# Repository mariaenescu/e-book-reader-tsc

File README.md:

Enescu Maria - 331CA

# OpenBook Project - E-Book Reader

OpenBook is a compact device designed for digital reading. Based on the ESP32-C6 microcontroller, OpenBook includes integrated Wi-Fi connectivity.
It features a 7.5" e-Paper display and an 1800mAh battery, offering extended battery life.

--- 

## 3D Visualizations

---
## Block Diagram

---

## Main Components Overview

**Microcontroller – ESP32-C6-WROOM-1-N8**  
Acts as the main processing unit of the system, responsible for wireless communication, power management, and control of all peripherals. It uses SPI, I2C, and GPIO interfaces to interact with external modules.

**E-Paper Display – 7.5” Waveshare**  
Displays e-book content using ultra-low power. It is controlled via SPI and connected through MOSI, MISO, SCK, CS, DC, RST, and BUSY pins.

**MicroSD Card – 112A-TAAR-R03**  
Used for storing e-books and data files. Communicates with the ESP32 via the SPI interface and supports FAT32 format up to 32GB.

**NOR Flash Memory – W25Q512JVEIQ**  
Provides external non-volatile memory for storing firmware or additional data. It connects via SPI and supports fast read/write operations.

**Real-Time Clock – DS3231SN**  
Ensures accurate timekeeping, even when the device is off. It uses the I2C protocol and provides a 32KHz output and interrupt signal.

**Environmental Sensor – BME688**  
Measures temperature, humidity, pressure, and gas levels. Communicates via I2C and is powered through a dedicated I2C power pin.

**Battery – Cellevia LP584174 (Li-Po 3.7V, 1800mAh)**  
Powers the system when disconnected from USB. Provides stable operation and extended autonomy.

**Power Management – MCP73831 & AMS1117**  
MCP73831 handles Li-Po charging via USB-C. AMS1117 regulates the output voltage to 3.3V required by the ESP32 and peripherals.

**USB-C Connector – USB4110-GF-A**  
Used for charging the battery and data transfer. Protected by ESD varistor (PFMF.050.1) and Schottky diode for reverse polarity.

**Buttons – Tactile Push Buttons (3x)**  
Used for boot, reset, and mode change. Connected to GPIOs for user input and state control.

---

## Bill of Materials
| Compound                | Purchase                          | Datasheet                                                                                                                                                          |
|---------------------------|--------------------------------------------------------------------------------------------------------------------------------------------------------------------------------------------------------------------------------------------------------------------|--------------------------------------------------------------------------------------------------------------------------------------------------------------------|
| Buton                     | [Click here](https://componentsearchengine.com/prices/TSP1C-RA?manufacturer=KNITTER-SWITCH)                                                                                                                                                                        | https://docs.rs-online.com/1fd0/0900766b80e2c247.pdf                                                                                                   |
| Condensator 100nF         | [Click here](https://ro.mouser.com/ProductDetail/KYOCERA-AVX/04026D104KAT2A?qs=LLG2yGGJ5NhILwMziGI8Xg%3D%3D)                                                                                                                                                       | https://www.mouser.com/catalog/supplier/library/pdf/AVXSurfaceMountCeramic.pdf                                                                         |
| CPH3225A(C10_SUPERCAP)    | [Click here](https://ro.mouser.com/ProductDetail/Seiko-Semiconductors/CPH3225A?qs=3etwrb1wR%252BhUOph6lAO7eg%3D%3D)                                                                                                                                                | https://ro.mouser.com/datasheet/2/360/Seiko_Instruments_MicroBattery_E_20230330_2024Jan_-3561061.pdf                                                   |
| Condensator 4.7uF         | [Click here](https://ro.mouser.com/ProductDetail/KEMET/C0402C475M7PACTU?qs=SzIX745sIXFB9Q9KfZhc4g%3D%3D)                                                                                                                                                           | https://ro.mouser.com/datasheet/2/447/KEM_C1006_X5R_SMD-3316465.pdf                                                                                    |
| Tantalum Condensator 100uF | [Click here](https://ro.mouser.com/ProductDetail/KYOCERA-AVX/TAJW107M010RNJ?qs=Wtp%252Bf%2FAeVqIH8v1VxV%252B1Rg%3D%3D)                                                                                                                                             | https://ro.mouser.com/datasheet/2/40/TAJ-3165264.pdf                                                                                                   |
| Condensator 1uF           | [Click here](https://ro.mouser.com/ProductDetail/KYOCERA-AVX/04026D105KAT2A?qs=LLG2yGGJ5NgAzk5fb%252BnzGQ%3D%3D)                                                                                                                                                   | https://ro.mouser.com/datasheet/2/40/cx5r_KGM-3223198.pdf                                                                                              |
| Condensator 10uF          | [Click here](https://www.digikey.com/en/products/detail/venkel/C0402X5R100-106MNP/12327194)                                                                                                                                                                        | https://venkelecd.com/partnumber/datasheet/C0402X5R100-106MNP)                                                                                         |
| CHG_LED                   | [Click here](https://www.kingbrightusa.com/distyPNInv.asp?sltSearch=distyInv&match=1&txtPartNo=APHM1608ECT)                                                                                                                                                        | https://www.kingbrightusa.com/images/catalog/SPEC/APHM1608ECT.pdf                                                                                      |
| USBLC6-2SC6Y              | [Click here](https://ro.mouser.com/ProductDetail/STMicroelectronics/USBLC6-2SC6Y?qs=gNDSiZmRJS%2FOgDexvXkdow%3D%3D)                                                                                                                                                | https://ro.mouser.com/datasheet/2/389/usblc6_2sc6y-1852505.pdf                                                                                         |
| PGB1010603MR              | [Click here](https://ro.mouser.com/ProductDetail/Littelfuse/PGB1010603MR?qs=gu7KAQ731URLg4GSnNNN7Q%3D%3D)                                                                                                                                                          | https://www.littelfuse.com/assetdocs/pulseguard-esd-suppressors-pgb1-datasheet?assetguid=8a337998-d54d-466b-be4e-dc5bcd1f9321                          |
| SD0805S020S1R0            | [Click here](https://ro.mouser.com/ProductDetail/KYOCERA-AVX/SD0805S020S1R0?qs=jCA%252BPfw4LHbpkAoSnwrdjw%3D%3D)                                                                                                                                                   | https://ro.mouser.com/datasheet/2/40/schottky-3165252.pdf                                                                                              |
| MBR0530                   | [Click here](https://ro.mouser.com/ProductDetail/onsemi/MBR0530T1G?qs=3JMERSakeboS%2FFOxJUMWeg%3D%3D)                                                                                                                                                              | https://www.onsemi.com/download/data-sheet/pdf/mbr0530t1-d.pdf                                                                                         |
| Condensator 1uF/50V       | [Click here](https://ro.mouser.com/ProductDetail/KYOCERA-AVX/06035D105MAT2A?qs=k4kUdCzLgS5%252BURKe1SOIeQ%3D%3D)                                                                                                                                                   | https://ro.mouser.com/datasheet/2/40/cx5r_KGM-3223198.pdf                                                                                              |
| Condensator 0.1uF/50V     | [Click here](https://ro.mouser.com/ProductDetail/KYOCERA-AVX/04025C104JAT2A?qs=yqaQSyyJnNjAUYBPnTRwrw%3D%3D)                                                                                                                                                       | https://ro.mouser.com/datasheet/2/40/AutoMLCC-2952695.pdf                                                                                              |
| BD5229G-TR                | [Click here](https://ro.mouser.com/ProductDetail/ROHM-Semiconductor/BD5229G-TR?qs=4kLU8WoGk0vvnhrrYwdszw%3D%3D)                                                                                                                                                    | https://fscdn.rohm.com/en/products/databook/datasheet/ic/power/voltage_detector/bd52xxg-e.pdf                                                          |
| XC6220A331MR-G            | [Click here](https://ro.mouser.com/ProductDetail/Torex-Semiconductor/XC6220A331MR-G?qs=AsjdqWjXhJ8ZSWznL1J0gg%3D%3D)                                                                                                                                               | https://ro.mouser.com/datasheet/2/760/xc6220-3371556.pdf                                                                                               |
| FH34SRJ-24S-0.5SH_99_     | [Click here](https://ro.mouser.com/ProductDetail/Hirose-Connector/FH34SRJ-24S-0.5SH99?qs=vcbW%252B4%252BSTIpKBl5ap9J8Fw%3D%3D)                                                                                                                                     | https://ro.mouser.com/datasheet/2/185/FH34SRJ_24S_0_5SH_99__CL0580_1255_6_99_2DDrawing_0-1615044.pdf                                                   |
| USB4110-GF-A              | [Click here](https://ro.mouser.com/ProductDetail/GCT/USB4110-GF-A?qs=KUoIvG%2F9IlYiZvIXQjyJeA%3D%3D)                                                                                                                                                               | https://ro.mouser.com/datasheet/2/837/GCT_USB4110_Product_Drawing___20k_cycles-3455479.pdf                                                             |
| QWIIC_RIGHT_ANGLE         | [Click here](https://ro.mouser.com/ProductDetail/JST-Commercial/SM04B-SRSS-TBLFSN?qs=cdbOS8ANM9B3FdyA6cNU2A%3D%3D)                                                                                                                                                 | https://ro.mouser.com/datasheet/2/564/eSR_SZ-3476820.pdf                                                                                               |
| 112A-TAAR-R03_ATTEND      | [Click here](https://www.tme.eu/ro/details/mcc-sdmicro/conectori-pentru-cartele/attend/112a-taar-r03/?utm_source=google&utm_medium=cpc&utm_campaign=RUMUNIA%20%5BP%5D%5BDC%5D&gclsrc=aw.ds&gad_source=1&gclid=Cj0KCQjwhr6_BhD4ARIsAH1YdjAAB3boEl8CsGuWhO_BI6GGNh3SIUi2gO3ftspK5-ah9niT38KGMasaAnHZEALw_wcB) | https://www.attend.com.tw/data/download/file/112A-TAAR-R03.pdf                                                                                         |
| Bobina                    | [Click here](https://ro.mouser.com/ProductDetail/Wurth-Elektronik/744043680?qs=PGXP4M47uW6VkZq%252BkzjrHA%3D%3D)                                                                                                                                                   | https://www.we-online.com/components/products/datasheet/744043680.pdf                                                                                  |
| MCP73831                  | [Click here](https://ro.mouser.com/ProductDetail/Microchip-Technology/MCP73831T-2ATI-OT?qs=yUQqVecv4qsZbioEUu%252B83g%3D%3D)                                                                                                                                       | https://ro.mouser.com/datasheet/2/268/MCP73831_Family_Data_Sheet_DS20001984H-3441711.pdf                                                               |
| PFMF.050.1                | [Click here](https://ro.mouser.com/ProductDetail/Schurter/PFMF.050.2?qs=1auRipcfynCums5v1iucSA%3D%3D)                                                                                                                                                              | https://ro.mouser.com/datasheet/2/358/typ_PFMF-1275918.pdf                                                                                             |
| DMG2305UX-7               | [Click here](https://ro.mouser.com/ProductDetail/Diodes-Incorporated/DMG2305UX-7?qs=L1DZKBg7t5F%2FNBHrjfxC%252Bg%3D%3D)                                                                                                                                            | https://www.diodes.com/assets/Datasheets/DMG2305UX.pdf                                                                                                 |
| SI1308EDL-T1-GE3          | [Click here](https://ro.mouser.com/ProductDetail/Vishay-Semiconductors/SI1308EDL-T1-GE3?qs=bX1%252BNvsK%2FBramh9tgpOaEw%3D%3D)                                                                                                                                     | https://www.vishay.com/docs/63399/si1308edl.pdf                                                                                                        |
| Rezistenta 10K            | [Click here](https://www.digikey.com/en/products/detail/venkel/CR0402-10W-102JT/12332774)                                                                                                                                                                          | https://data.venkel.com/documents/cr-series?_gl=1*2989pu*_ga*Nzc4NDIxNDY2LjE3NDM3NTUzNDM.*_ga_JRKGBZNVM8*MTc0Mzc1NTM0My4xLjAuMTc0Mzc1NTM0My42MC4wLjA.) |
| Rezistenta 200            | [Click here](https://ro.mouser.com/ProductDetail/Vishay-Beyschlag/MCS0402MD2000BE100?qs=3SvaY9RawMJNVte4F12%252BZQ%3D%3D)                                                                                                                                          | https://www.vishay.com/docs/28952/mcs0402at-mct0603at-mcu0805at-mca1206at.pdf                                                                          |
| Rezistenta 100K           | [Click here](https://www.digikey.com/en/products/detail/venkel/CR0402-16W-1003FT/12328296)                                                                                                                                                                         | https://octopart.com/datasheet/cr0402-16w-1003ft-venkel-16112934)                                                                                      |
| Rezistenta 2.2            | [Click here](https://www.digikey.com/en/products/detail/venkel/TFCR0402-16W-C-1002BT/12331302)                                                                                                                                                                     | https://data.venkel.com/documents/tfcr-series?_gl=1*1o1n72f*_ga*Nzc4NDIxNDY2LjE3NDM3NTUzNDM.*_ga_JRKGBZNVM8*MTc0Mzc1NTM0My4xLjEuMTc0Mzc1NjA4Mi4yMi4wLjA.) |
| Rezistenta 5K1            | [Click here](https://ro.mouser.com/ProductDetail/YAGEO/RT0402BRD075K1L?qs=gY0y7AQI9SOxpEAvlEsiTQ%3D%3D)                                                                                                                                                            | https://ro.mouser.com/datasheet/2/447/PYu_RT_1_to_0_01_RoHS_L_15-3461507.pdf                                                                           |
| Rezistenta 2K             | [Click here](https://ro.mouser.com/ProductDetail/Bourns/CR0402AFX-2001GLF?qs=GedFDFLaBXEKjamDtfYtIQ%3D%3D)                                                                                                                                                         | https://ro.mouser.com/datasheet/2/54/cr_a-1858337.pdf                                                                                                  |
| Rezistenta 0.47           | [Click here](https://ro.mouser.com/ProductDetail/Vishay-Beyschlag/MMA02040C4707JB000?qs=YmMt7wOBEV42V6C1Rc7zpg%3D%3D)                                                                                                                                              | https://www.vishay.com/docs/28713/melfprof.pdf                                                                                                         |
| Rezistenta 15             | [Click here](https://ro.mouser.com/ProductDetail/YAGEO/RT0402FRE0715RL?qs=BXCcY9r%252B08DFFpLSkPOIqQ%3D%3D)                                                                                                                                                        | https://ro.mouser.com/datasheet/2/447/PYu_RT_1_to_0_01_RoHS_L_15-3461507.pdf                                                                           |
| BME688                    | [Click here](https://ro.mouser.com/ProductDetail/Bosch-Sensortec/BME688?qs=IS%252B4QmGtzzqQoVDscqwx3A%3D%3D)                                                                                                                                                       | https://ro.mouser.com/datasheet/2/783/bst_bme688_fl000-2307034.pdf                                                                                     |
| W25Q512JVEIQ              | [Click here](https://ro.mouser.com/ProductDetail/Winbond/W25Q512JVEIQ?qs=l7cgNqFNU1jw6svr3at6tA%3D%3D)                                                                                                                                                             | https://ro.mouser.com/datasheet/2/949/Winbond_W25Q512JV_Datasheet-3240039.pdf                                                                          |
| ESP32-C6-WROOM-1-N8       | [Click here](https://ro.mouser.com/ProductDetail/Espressif-Systems/ESP32-C6-WROOM-1-N8?qs=8Wlm6%252BaMh8ST02Gmwp74cw%3D%3D)                                                                                                                                        | https://ro.mouser.com/datasheet/2/891/Espressif_ESP32_C6_WROOM_1__Datasheet_V0_1_PRELIMI-3239987.pdf                                                   |
| DS3231SN#                 | [Click here](https://ro.mouser.com/ProductDetail/Analog-Devices-Maxim-Integrated/DS3231SN?qs=1eQvB6Dk1vhUlr8%2FOrV0Fw%3D%3D)                                                                                                                                       | https://ro.mouser.com/datasheet/2/609/DS3231-3421123.pdf                                                                                               |
| MAX17048G+T10             | [Click here](https://ro.mouser.com/ProductDetail/Analog-Devices-Maxim-Integrated/MAX17048G%2bT10?qs=D7PJwyCwLAoGnnn8jEPRBQ%3D%3D)                                                                                                                                  | https://ro.mouser.com/datasheet/2/609/MAX17048_MAX17049-3469099.pdf                                                                                    |
---

## Hardware Functionality Description

The project uses the `ESP32-C6-WROOM-1-N8` microcontroller, which integrates **BLE 5** and **Wi-Fi 6** for fast and efficient communication.
The system is powered by a **3.7V Li-Po battery** with a capacity of 1800mAh (`Cellevia LP584174`).
Battery charging is managed by the `TP4056` module via a `USB-C` connector, and the constant `3.3V` required by the system is provided by an `AMS1117` voltage regulator.
The `ESP32-C6` microcontroller controls the entire system through standard **SPI**, **I2C**, and **GPIO** interfaces, as follows:
1. The `7.5" Waveshare e-Paper Display` (800x480 resolution) is connected via SPI.
2. The `SD Card` and `external NOR Flash` memory are also connected via SPI for data storage.
3. The `RTC (DS3231SN)` and `environmental sensor (BME688)` are connected via **I2C**, enabling precise real-time measurements.
4. **GPIO connections** allow control of the `RESET` and `BOOT` functions, and the **Qwiic/Stemma QT** interface supports additional sensor expansion.
5. For debugging, there are dedicated Test Pads for UART communication (`TX/RX`).

---

##  Pinii ESP32-C6
| Pin ESP32-C6 | GPIO        | Job            | Connected to          |
|--------------|-------------|--------------------|------------------------|
| EN           | -           | RESET              | Reset hardware         |
| IO0          | GPIO0       | INT RTC            | Intrerupere RTC        |
| IO1          | GPIO1       | 32KHZ              | Semnal 32kHz RTC       |
| IO2          | GPIO2       | MISO               | SPI MISO (Date citite) |
| IO3          | GPIO3       | EPD BUSY           | Semnal ocupat Display  |
| IO4          | GPIO4       | SS_SD              | Chip select SD Card    |
| IO5          | GPIO5       | EPD_DC             | Comanda/Date Display   |
| IO6          | GPIO6       | SCK                | SPI Clock              |
| IO7          | GPIO7       | MOSI               | SPI MOSI (Date trimise)|
| IO8          | GPIO8       | IO/BOOT            | Boot mode selection    |
| IO9          | GPIO9       | -                  | Neconectat             |
| IO10         | GPIO10      | -                  | Neconectat             |
| IO11         | GPIO11      | EPD_CS             | Chip Select Display    |
| IO12         | GPIO12      | FLASH_CS           | Chip Select Flash      |
| IO13         | GPIO13      | USB D-             | Linie USB D-           |
| IO14         | GPIO14      | USB D+             | Linie USB D+           |
| IO15         | GPIO15      | IO/CHANGE          | Buton schimbare mod    |
| IO16         | GPIO16/TX   | TX                 | UART Debug TX          |
| IO17         | GPIO17/RX   | RX                 | UART Debug RX          |
| IO18         | GPIO18      | RTC_RST            | Reset RTC              |
| IO19         | GPIO19      | I2C PW             | Alimentare senzor I2C  |
| IO20         | GPIO20      | EPD_3V3_C          | Control 3.3V Display   |
| IO21         | GPIO21/SDA  | SDA                | I2C Date               |
| IO22         | GPIO22/SCL  | SCL                | I2C Clock              |
| IO23         | GPIO23      | EPD_RST            | Reset Display          |
---

## Project Implementation:
      
`The schematic` was created according to the requirement PDF, using symbols from the provided library and verified using 
the `ERC` file. Warnings were avoided, and remaining errors were accepted as non-critical.
During the `PCB` design phase, all components were placed exclusively on the `Top Layer`, following mechanical and dimensional recommendations.
Both the `ESP32 antenna area` and the `buttons` were cut out from the PCB outline.
`Routing` was performed using the Autorouter, with a 100% routing weight and minimum via size.
A `ground plane` was created on both layers (Bottom and Top).
`Via stitching` was added near the ESP32 component in a free area, avoiding routing traces.
Each component name is marked with `TopSilkscreen`.
Each component has an associated 3D model, either designed (TPs, battery, and display) or imported from external libraries.
The 3D models were created using exact dimensions from the provided datasheets and can be viewed in the `Images/` folder.
Later, I positioned the 3D model of the PCB, the battery, and the display inside the case.
A video has also been added in `Images/` to visualize the 3D placement of all components for the complete E-Book.

---

### Issues Encountered:

- After importing each 3D component, I noticed several routing errors and value mismatches appearing on the PCB—
  errors that did not exist before using `Push to 3D PCB`. After adding the 3D components, I attempted to re-route to fix these issues.
- I encountered problems with 3D component placement. Although all 3D models were imported, not all of them appeared on the 3D PCB.
- In **Fusion 360**, `Push to 3D PCB` sometimes desynchronized component labels and layers. Also, not all components kept their footprints aligned after 3D model imports, requiring manual corrections.
- I also had to ensure no 90° trace angles were present, per assignment constraints — which was hard to maintain while autorouting.

---

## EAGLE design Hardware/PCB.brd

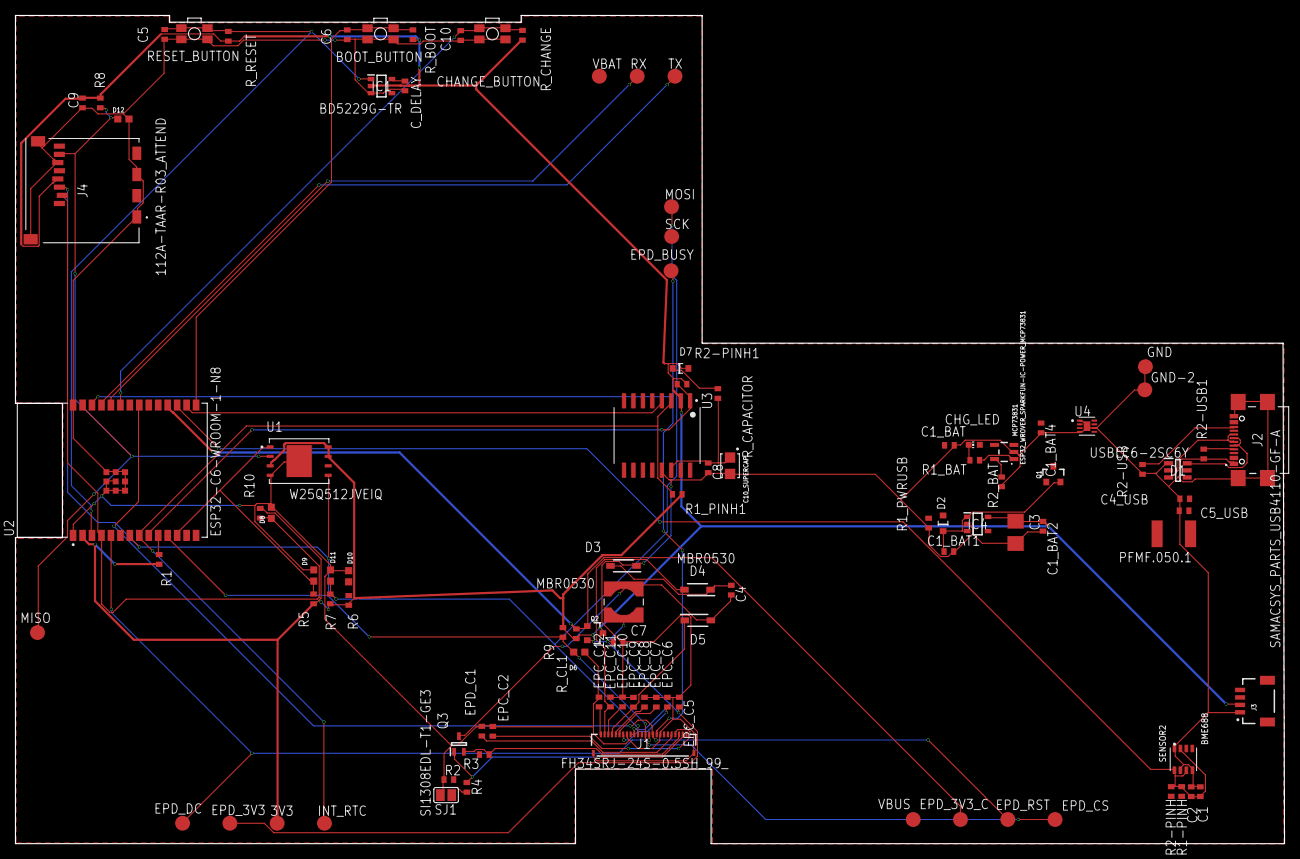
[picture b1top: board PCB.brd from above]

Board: 2 copper layers, 170.4 x 111.2 mm, 103 parts (0 on the bottom side), 46 nets.

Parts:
3V3: TPTP20R; TP20R
BOOT_BUTTON: BUTTON_CUSYOMV1; MYBUTTON
C1, C2, C4_USB, C6, C8, C9, C10: 100nF; EAGLE-LTSPICE_C0402
C1_BAT, C1_BAT1, C1_BAT2, C1_BAT4, C5_USB: 4.7uF; EAGLE-LTSPICE_C0402
C3: 100uF; RCL_CT3528
C4: 4.7uF/25V; EAGLE-LTSPICE_C0402
C5: 1uF; EAGLE-LTSPICE_C0402
C7: 10uF; EAGLE-LTSPICE_C0402
C10_SUPERCAP: CPH3225A; CAPCP3225X100N
CHANGE_BUTTON: BUTTON_CUSYOMV1; MYBUTTON
CHG_LED: ADAFRUIT_CHIP-LED0603
C_DELAY: 100nF; EAGLE-LTSPICE_C0402
D1: USBLC6-2SC6Y; SOT95P280X145-6N
D2: ESP32_WROVER_AVX---SD0805S020S1R0_AVX_SD0805S020S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; ESP32_WROVER_AVX---SD0805S020S1R0_AVX_SD0805S020S1R0_0
D3, D4, D5: MBR0530; SOD3716X135N
D6, D8, D9, D10, D11, D12: PGB1010603MR; DIOC1608X36N
D7: SD0805S020S1R0; ESP32_WROVER_AVX---SD0805S020S1R0_AVX_SD0805S020S1R0_0
EPC_C2, EPC_C5, EPC_C6, EPC_C7, EPC_C8, EPC_C9, EPC_C10, EPC_C11, EPC_C12: 1uF/50V; ESP32_WROVER_EAGLE-LTSPICE_C0402
EPD_3V3, EPD_3V3_C: TPTP20R; TP20R
EPD_BUSY: TPTP20R; TP20R
EPD_C1: 1uF/50V; ESP32_WROVER_EAGLE-LTSPICE_C0402
EPD_CS: TPTP20R; TP20R
EPD_DC: TPTP20R; TP20R
EPD_RST: TPTP20R; TP20R
GND: TPTP20R; TP20R
GND-2: TPTP20R; TP20R
IC1: BD5229G-TR; SOT95P280X125-5N
IC4: XC6220A331MR-G; SOT95P280X120-5N
INT_RTC: TPTP20R; TP20R
J1: FH34SRJ-24S-0.5SH_99_; FH34SRJ24S05SH99
J2: SAMACSYS_PARTS_USB4110-GF-A; SAMACSYS_PARTS_USB4110GFA
J3: QWIIC_RIGHT_ANGLE; JST04_1MM_RA
J4: 112A-TAAR-R03_ATTEND; 112ATAARR03ATTEND
L1: 68uH; IND_4828-WE-TPC_WRE
MCP73831: ESP32_WROVER_SPARKFUN-IC-POWER_MCP73831; ESP32_WROVER_SPARKFUN-IC-POWER_SOT23-5
MISO: TPTP20R; TP20R
MOSI: TPTP20R; TP20R
PFMF.050.1: ESP32C6_VARISTORCN1812; ESP32C6_VARISTOR_CT/CN1812
Q1, Q2: 20V/4.2A/52mΩ/1.4W; ESP32_WROVER_SPARKFUN-DISCRETESEMI_SOT23-3
Q3: SI1308EDL-T1-GE3; SOT65P210X110-3N
R1, R1-PINH, R1_PINH1, R2-PINH, R2-PINH1, R4, R5, R6, R7, R8, R9, R10: 10K; ESP32_WROVER_EAGLE-LTSPICE_R0402
R1_BAT: 200; ESP32_WROVER_EAGLE-LTSPICE_R0402
R1_PWRUSB: 100K; ESP32_WROVER_EAGLE-LTSPICE_R0402
R2: 2.2; ESP32_WROVER_EAGLE-LTSPICE_R0402
R2-USB, R2-USB1: 5k1; ESP32_WROVER_EAGLE-LTSPICE_R0402
R2_BAT: 2K; ESP32_WROVER_EAGLE-LTSPICE_R0402
R3: 0.47; ESP32_WROVER_EAGLE-LTSPICE_R0402
RESET_BUTTON: BUTTON_CUSYOMV1; MYBUTTON
RX: TPTP20R; TP20R
R_BOOT: 10K; ESP32_WROVER_EAGLE-LTSPICE_R0402
R_CAPACITOR: 15; ESP32_WROVER_EAGLE-LTSPICE_R0402
R_CHANGE: 10K; ESP32_WROVER_EAGLE-LTSPICE_R0402
R_CL1: 10K; ESP32_WROVER_EAGLE-LTSPICE_R0402
R_RESET: 10K; ESP32_WROVER_EAGLE-LTSPICE_R0402
SCK: TPTP20R; TP20R
SENSOR2: BME688; ESP32_WROVER_BME680_PSON80P300X300X100-8N
SJ1: SJ
TX: TPTP20R; TP20R
U1: W25Q512JVEIQ; SON127P600X800X80-9N
U2: ESP32-C6-WROOM-1-N8; XCVR_ESP32-C6-WROOM-1-N8
U3: DS3231SN#; SOIC127P1032X265-16N
U4: MAX17048G+T10; SON50P200X200X80-9N
VBAT: TPTP20R; TP20R
VBUS: TPTP20R; TP20R

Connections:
3V3: 3V3.TP, C1_BAT2.1, C3.+, C9.1, D7.2, IC1.2, IC4.5, J3.2, J4.P4, Q2.3, R1.2, R1_PINH1.2, R2-PINH1.2, R5.2, R6.2, R7.2, R8.2, R9.2, R10.2, R_BOOT.1, R_CHANGE.1, R_CL1.1, R_RESET.1, U1.3, U1.7, U1.8, U2.2, U3.2
12C_PW: C1.1, C2.1, R1-PINH.2, R2-PINH.2, SENSOR2.2, SENSOR2.6, SENSOR2.8, U2.17
32KHZ: R2-PINH1.1, U2.9, U3.1
DN: D1.6, J2.A7, J2.B7
DP: D1.3, J2.A6, J2.B6
EPD_3V3: C7.1, EPC_C5.2, EPD_3V3.TP, J1.15, J1.16, L1.2, Q2.2
EPD_3V3_C: EPD_3V3_C.TP, Q2.1, R_CL1.2, U2.18
EPD_BUSY: EPD_BUSY.TP, J1.9, U2.26
EPD_CS: D6.1, EPD_CS.TP, J1.12, R9.1, U2.11
EPD_DC: EPD_DC.TP, J1.11, U2.5
EPD_RST: EPD_RST.TP, J1.10, U2.21
FLASH_CS: D9.1, R5.1, U1.1, U2.12
GDR: J1.2, Q3.1, R4.2
GND: BOOT_BUTTON.1, BOOT_BUTTON.2, C1.2, C1_BAT.2, C1_BAT1.2, C1_BAT2.2, C1_BAT4.2, C2.2, C3.-, C4_USB.2, C5.2, C5_USB.2, C6.2, C7.2, C8.2, C9.2, C10.2, C10_SUPERCAP.2, CHANGE_BUTTON.1, CHANGE_BUTTON.2, C_DELAY.2, D1.1, D3.1, D6.2, D8.2, D9.2, D10.2, D11.2, D12.2, EPC_C2.1, EPC_C5.1, EPC_C6.1, EPC_C7.1, EPC_C8.1, EPC_C9.1, EPC_C10.1, EPC_C11.1, EPC_C12.1, EPD_C1.1, GND.TP, GND-2.TP, IC1.3, IC4.2, J1.8, J1.17, J1.MP1, J1.MP2, J2.A1, J2.A12, J2.B1, J2.B12, J2.MP1, J2.MP2, J2.MP3, J2.MP4, J3.1, J4.G1, J4.G2, J4.G3, J4.G4, J4.P6, MCP73831.2, R1_PWRUSB.1, R2.1, R2-USB.2, R2-USB1.1, R2_BAT.1, R4.1, RESET_BUTTON.1, RESET_BUTTON.2, SENSOR2.1, SENSOR2.5, SENSOR2.7, SJ1.1, U1.4, U1.9, U2.1, U2.28, U2.29_1, U2.29_2, U2.29_3, U2.29_4, U2.29_5, U2.29_6, U2.29_7, U2.29_8, U2.29_9, U3.13, U4.1, U4.4, U4.6, U4.9
GPIO8: R1.1, U2.10
INT_RTC: INT_RTC.TP, R1_PINH1.1, U2.8, U3.3
IO/BOOT: BOOT_BUTTON.3, BOOT_BUTTON.4, C6.1, R_BOOT.2, U2.15
IO/CHANGE: C10.1, CHANGE_BUTTON.3, CHANGE_BUTTON.4, R_CHANGE.2, U2.23
MISO: D12.1, J4.P7, MISO.TP, R8.1, U1.2, U2.27
MOSI: D11.1, J1.14, J4.P3, MOSI.TP, R7.1, U1.5, U2.7
unnamed: C1_BAT1.1, D2.1, IC4.1, IC4.3, Q1.2
unnamed: J2.B5, R2-USB.1
unnamed: J2.A5, R2-USB1.2
unnamed: C_DELAY.1, IC1.5
unnamed: C4.1, D3.2, D4.1
unnamed: MCP73831.1, R1_BAT.2
unnamed: CHG_LED.C, R1_BAT.1
unnamed: MCP73831.5, R2_BAT.2
unnamed: EPC_C12.2, J1.24
unnamed: D7.1, R_CAPACITOR.1
unnamed: EPC_C10.2, J1.22
unnamed: EPC_C8.2, J1.20
unnamed: EPC_C7.2, J1.19
unnamed: EPC_C6.2, J1.18
unnamed: EPC_C2.2, J1.5
unnamed: EPD_C1.2, J1.4
PREVGH: D5.1, EPC_C9.2, J1.21
PREVGL: D4.2, EPC_C11.2, J1.23
RESE: J1.3, Q3.2, R3.2
RESET: C5.1, IC1.1, RESET_BUTTON.3, RESET_BUTTON.4, R_RESET.2, U2.3
RTC_RST: U2.16, U3.4
RX: RX.TP, U2.24
SRC: C4.2, D5.2, L1.1, Q3.3
SS_SD: D8.1, J4.P2, R10.1, U2.4
TX: TX.TP, U2.25
VRTC: C8.1, C10_SUPERCAP.1, R_CAPACITOR.2, U3.14

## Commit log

2025-04-05 Rename LICENSE.txt to LICENSE
2025-04-10 Resolve Issue #1
2025-04-10 Resolve Issue #2
2025-04-10 Resolve Issue #3
2025-04-10 Resolve Issue #4

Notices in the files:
parts and their libraries:
COPYRIGHT: Copyright (C) 2024 Ultra Librarian. All rights reserved.
